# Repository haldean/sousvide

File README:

Dependencies:
	github.com/ajstarks/svgo

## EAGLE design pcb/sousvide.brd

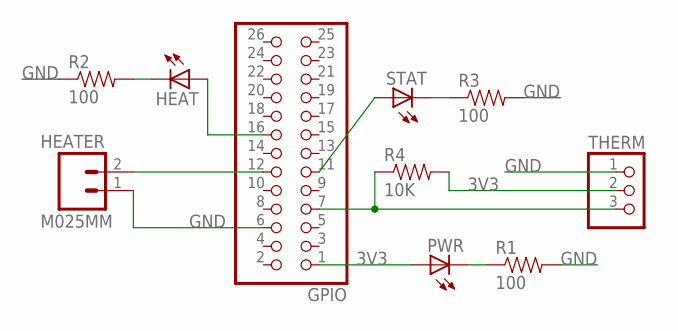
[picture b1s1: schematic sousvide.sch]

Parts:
GPIO: PINHD-2X13; 2X13
HEAT: LED1206; LED-1206
HEATER: M025MM; SCREWTERMINAL-5MM-2
PWR: LED1206; LED-1206
R1, R2, R3: 100; 1206
R4: 10K; 1206
STAT: LED1206; LED-1206
THERM: PINHD-1X3; 1X03

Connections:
3V3: GPIO.1, PWR.A, R4.2, THERM.2
GND: GPIO.6, HEATER.1, R1.2, R2.1, R3.2, THERM.1
unnamed: PWR.C, R1.1
unnamed: GPIO.12, HEATER.2
unnamed: R3.1, STAT.C
unnamed: GPIO.16, HEAT.A
unnamed: HEAT.C, R2.2
unnamed: GPIO.11, STAT.A
unnamed: GPIO.7, R4.1, THERM.3

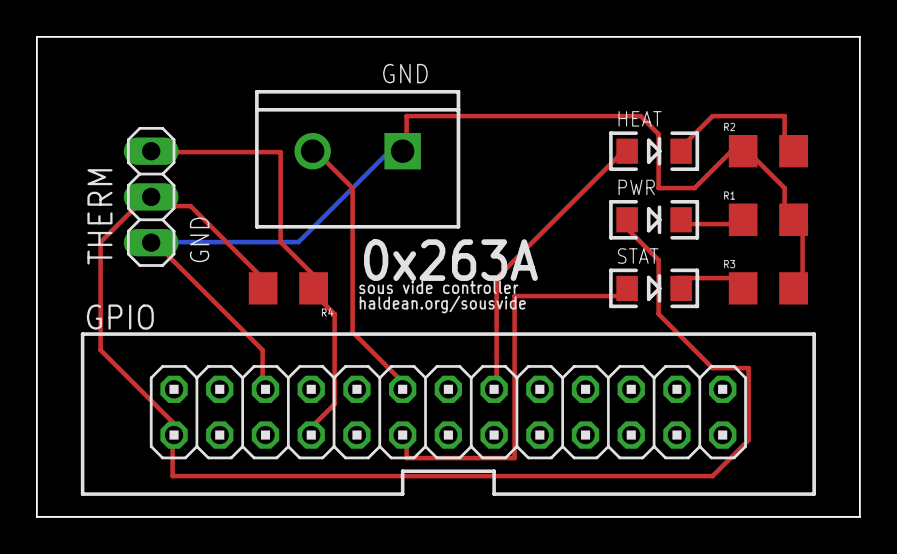
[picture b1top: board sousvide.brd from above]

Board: 2 copper layers, 45.7 x 26.7 mm, 10 parts (0 on the bottom side), 9 nets.

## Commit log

2013-07-28 Damn I did a lot of work on this without commiting.
    May I forever live in shame. This generates a live-updating site with fake data
    that allows for changing of the target temperature. It also generates SVG charts
    using vdobler's charts library. The dependencies in the README are a subset of
    the actual dependencies, I forgot to keep track until after I had started.
2013-07-28 Remove files that shouldn't be there.
    Also fix a small exception thrown when requests come in before data.
2013-07-29 Add ability to tune PID params from web interface
2013-07-30 Big refactor to make history easier to work with.
2013-07-30 Use process value for determining derivative in controller.
    This avoids issues in and around locations where the setpoint changes; you get
    _huge_ spikes in derivative when the setpoint changes if you take the derivative
    over error instead of process value.
2013-07-31 Add GPIO heater relay support.
2013-07-31 Add thermocouple support.
    Theoretically, I'm done!
2013-07-31 Who puts spaces in a filename. I mean seriously.
2013-07-31 Add fake temperature file, fix temperature parsing
2013-07-31 The thermocouple not being ready to read is not a fatal error.
2013-07-31 Fix small bug around buffering of therm output.
2013-08-05 A few fixes from testing.
    Changes:
    - Don't take out locks when reading; the rpi can't keep up
    - Set the default to be zero degrees
    - Increase the heater read interrupt timer
2013-08-05 Formatting fixes, better fake temp support.
2013-08-05 Add enable/disable status.
2013-08-05 Save PID values and load on start
2013-08-05 Add overshoot tracking to UI
2013-08-06 New chart backend working with raw SVG output.
    Needed to do this to allow for drawing when the heater is on/off in the graph.
2013-08-06 Switch to using polylines for graphing.
2013-08-07 Fix div-by-0 bug in chart generation.
2013-08-11 Add timers.
    Note that in-browser sounds don't work yet, the only indication that a
    timer is done is that it expires and the font turns red.
2013-08-11 Fix timer implementation, and make noise work.
2013-08-11 Some fixes for mobile clients.
2013-08-15 Add PCB source files to the repository.
2013-08-16 Increase history size to 4096
2013-08-16 Clean out gh-pages branch
2013-08-16 Add sous vide documentation
2013-08-16 Add last updated line
2013-08-17 MOBILE-FIRST
2013-08-17 Fixes for mobile
2013-08-18 More pictures!
2013-08-18 Improved control system copy
2013-08-18 Fix bug in PCB.
    The first one dropped too much over the LED in line with the heater relay, so
    the heater relay never flipped. This removes the LED in line with the heater and
    replaces it with an LED on a separate pin.
    Important lesson learned: always breadboard your designs before you fab them.
2013-08-18 New schematic and board design
2013-08-21 Switch to Roboto
2013-08-21 use new content stylesheets
2013-08-21 fix bad url
2013-10-09 Add PWM section
2013-10-16 trendyyyyy
2013-10-16 Starting to look pretty!
    Still missing plots, which is big, as well as temperature setting. Need some
    sort of ajaxy progress indicator for actions like enable/disable.
2013-10-16 Add loading indicator
2013-10-17 Pretty d3.js charts in the background!
2013-10-17 Implement animated theme switching because reasons
    Oh man now it does this awesome thing where it switches color when you
    switch it from enabled to disabled and it's super fucking sweet.
2013-10-17 Remove obsolete chart generation
    Long live the client side!
2013-10-17 Add a few files missing.
    oh by the way I switched from ender to jquery, whoops.
2013-10-17 Move timer JS into its own file
2013-10-17 More modularization, error mask
    Now there's a modal interstitial that pops up when api_data takes a
    long time at first, and it animates around really nicely because yay!
2013-10-17 Add temperature and PID editor.
    This is now (pretty much!) fully featured! I'm going to add some more
    animations because I fucking love animations.
2013-10-17 Change /target and /pid to be handled by /params
    This simplifies the form stuff a lot.
2013-10-18 Change blue secondary so black text looks better against it
2013-10-18 Add heating indicator
2013-10-18 Add readme
2013-10-18 Add ability to disable animations for slower platforms
2013-10-23 Add relay shield with compiled STL.
    The relay shield is used to mask the relay contacts so I can't
    electrocute myself quite as easily. It is _not_ an Arduino shield.
2013-10-23 Change relay shield to have slightly more accurate dims
2013-10-25 Rearrange shield for easier printing
2014-02-21 Starting to work on V3!
    Some minor fixes to the relay shield, and a new (boring) part, which is a mount
    for the heaters.
2014-02-23 Add vectors for platform part.
2014-02-23 Add gitignore
2014-03-24 Add broadcast capabilities.
    These are used for the Android app.
2014-03-24 Update UI section.

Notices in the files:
parts and their libraries:
SparkFun-Connectors: Licensing: CC v3.0 Share-Alike You are welcome to use this library for commercial purposes.
